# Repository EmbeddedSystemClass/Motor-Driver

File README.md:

# Motor-Driver

Collection of all boards past and presenet used by UOE Racing. Boards are organized by year of competition

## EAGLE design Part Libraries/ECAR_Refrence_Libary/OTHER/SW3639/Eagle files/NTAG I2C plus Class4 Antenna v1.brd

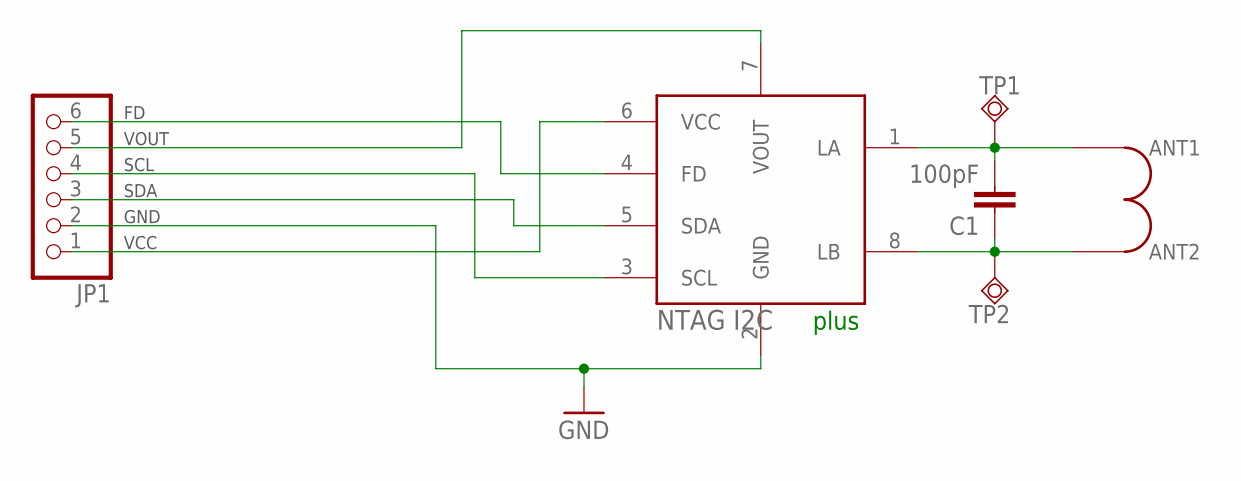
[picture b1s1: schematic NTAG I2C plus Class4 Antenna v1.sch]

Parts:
C1: 100pF; C0402K
JP1: PINHD-1X6/90; 1X06/90
TP1, TP2: TPSQPAD1-13; P1-13
U$1: ENERGY-HARVESTING_3-TURNS54X27_3TURN_THIN; 54X27_3TURNS_THIN
U$3: NTAG_I2CXQFN8; SOT902-3

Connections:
GND: JP1.2, U$3.2 (GND)
unnamed: C1.2, TP1.TP, U$1.ANT1, U$3.1 (LA)
unnamed: C1.1, TP2.TP, U$1.ANT2, U$3.8 (LB)
unnamed: JP1.1, U$3.6 (VCC)
unnamed: JP1.3, U$3.5 (SDA)
unnamed: JP1.4, U$3.3 (SCL)
unnamed: JP1.6, U$3.4 (FD)
unnamed: JP1.5, U$3.7 (VOUT)

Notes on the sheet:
VOUT
SCL
SDA
GND
VCC
plus

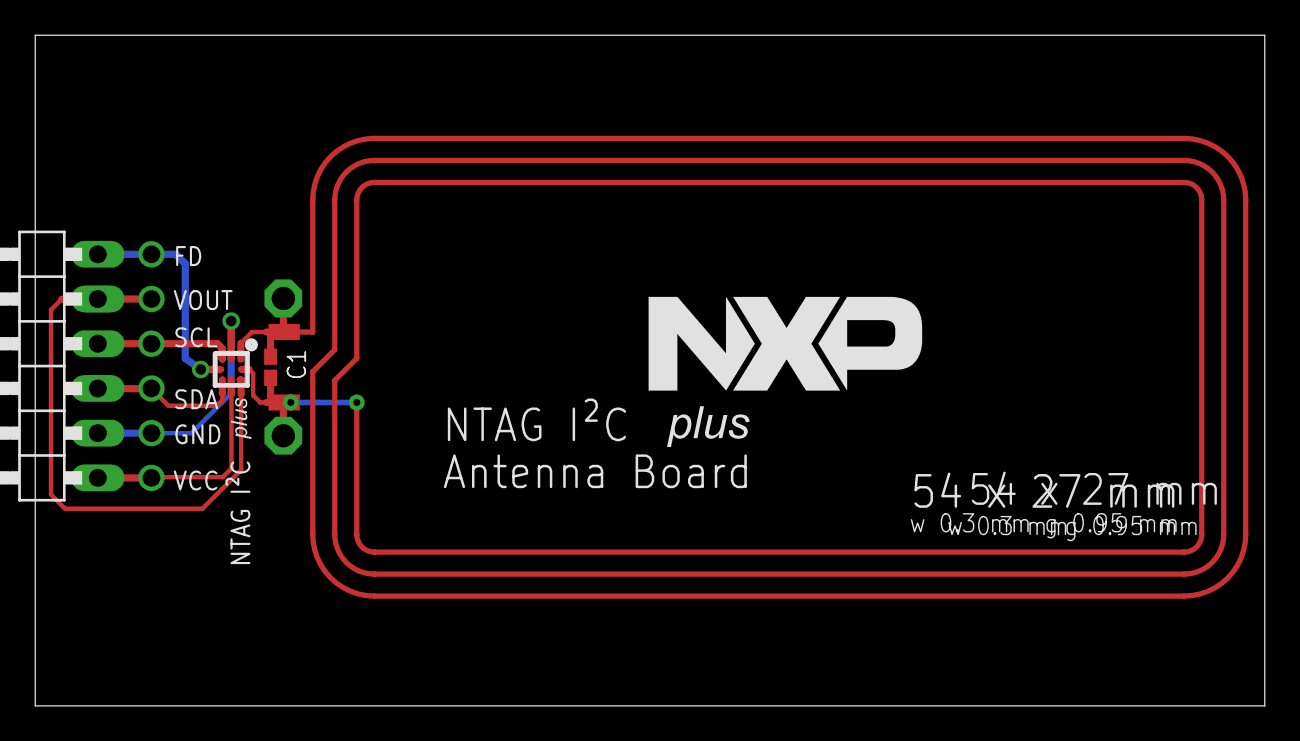
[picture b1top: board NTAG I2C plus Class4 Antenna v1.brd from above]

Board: 2 copper layers, 69.8 x 38.1 mm, 6 parts (0 on the bottom side), 8 nets.

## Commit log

2019-07-14 Addition of all files from 2018-2019
2019-07-14 Addition of part libaries and gitignore
2019-07-15 Creation of 2020 board project
2019-07-19 Reoranization
    Brought the old board project into Motor Folder 2019-2020
    Reorganization of project folder
2019-09-01 test1
2019-09-03 LM regulator
2019-09-15 changed net on nSHN
2019-09-25 Addition of input filter on throttle and the addition of the hall effect input digital gates (Schmitt and level translation)
2019-09-26 Fix of schematic layout and symbols for 3.3V and 5V power supply. Initial work on MOSFET power bridge
2019-09-27 Addition of SD Card, addition of the tempature sensors for Fets. Completion of motor driver chip circuit, completion of the FET power stage.
2019-09-27 Additon of the encoder input interface. Also added in the input connector circuits for the encoder and hall effect sensors
2019-10-10 A crazy amount of components added. MCU and Digital Interfaces and Connectors and Inputs schematic pages finished, same as Power section sheet
2019-10-17 Fixed Output Reg Pwr
2019-10-19 small adjustments to 3.3reg and renaming couple of components
2019-10-24 Some minor cosmetic fixes to the sheet
2019-11-01 Addition of power anaylsis
    Added the power analysis for the 3.3V and 5V power rials into the 2020 folder
2019-11-05 Addition of 5v regulator and led indication circuitry
2019-11-05 Generation of schematic for design review
2019-11-07 modification
    zero ohm resistors, labeling, zener, encoder enable
2019-11-08 Update ProjectGroup.DsnWrk
    Added to PMOS encoder enable configuration. Added parts
2019-11-15 Change of the throttle filter op-amp to address bandwidth and input bias problems. Also added simulation circuit and results in the simulation folder
2019-11-17 Re organization of a couple of schematic pages
2019-11-20 Checking of more blocks of the schematic.
    Removed the io expander, as its functionality is now covered by the expanded MCU socket.
    Changed the capacitors for the voltage input to the board. Simulated the voltage feedback circuit and then changed a resistor value to allow operation of the circuit up to 60V. Caps still need to be 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
2019-11-22 Addition of power filter simulation files
2019-11-25 some foot print changes and sanity checking
2019-11-25 sanity checking
2019-12-01 Changes to the schematic. Almost at completion
2019-12-03 Checking of the DRV circuit
2019-12-03 Fix of the led indicator circuits.
    Also changed the 47nF capacitor to have a rating of 100V so that the board can work at 60V (was 50V rated before)
2019-12-05 Verification of the FET bridge
2019-12-08 Update of the main power in connector to the bolt on board 4 pin variant. Should cut down on the amount of heating seen at the connector
2019-12-08 Change of main phase connector from 3 pin to 6 pin to increase current capability and allow for a more robust connector
2019-12-12 Final checks performed. Schematic should be ready for board creation
2020-01-03 Push of the initial layout
2020-01-04 Throttle section practice
2020-01-04 More practicing, placed Schmitt hall Schmit components
2020-01-05 Added the Encoder section
2020-01-05 net fixing
2020-01-05 moving buffer
2020-01-05 GPIO buffers and connectors
2020-01-06 Power section and driver chip finished
2020-01-11 Fix?
2020-01-11 Hopefully the right files
2020-01-13 Testest
    Commiting finaly
2020-01-15 placing GPIO buffer
    testing git
2020-01-15 More placing of test points
    git working
2020-01-16 Added 5v power
    Practicing with the polygon pour. May need to change and edit.
2020-01-16 Getting close to complete
2020-01-17 Revert "Merge branch 'master' of github.com:UOERacing/Motor-Driver"
    This reverts commit 896bb1447881fe9900ef6cad67ef5cf2d1325141, reversing
    changes made to bacd3aeafff96990d78e3a7c32f37b9bf0d5d698.
2020-01-18 Completion of routing
2020-01-19 Footprint fix, silk screen fixing and TP naming
2020-01-21 silk screen fixing
2020-01-22 Almost done silk screen
2020-01-23 Silk screen finished. Needs review
2020-01-23 Testing version control
2020-01-26 Change of mounting hole size to 3.5mm as per Simons instructions
2020-01-26 Minor silk correction and pass of the DRC
2020-01-27 Small finishing touches to the board. Now missing only logo for team
2020-01-27 Project ready for Review
2020-01-31 Footprint Fixes, Silk Screen Fix.
    Polygon pour at the 3v3 regulator Inductor needs some adjusting as well as some component placement
2020-02-03 Addition of Gerber files and fix of polygon attached to inductor. Slight silkscreen changes
2020-02-07 Tied the enable for the 3.3V regulator to the pwr good indicator of the 5V Regualtor
2020-02-08 Revert "na"
    This reverts commit 1781cdccb237cffe15a9127709c46b1f825b080e.
2020-02-11 Addition of enable pull up resistor on 3.3V regulator in case the power good line from 5V is not working correctly
2020-02-11 C13, 15, 16 rerouted due to voltage tolerances not being high enough . C15 changed to meet requirement and placed on board
2020-02-12 Capacitor Update finished
2020-02-16 ActiveBom File created
2020-02-27 Generation of RFM rev manufacturing files
2020-05-09 Additions to parts library for transmitter

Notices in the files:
parts and their libraries:
SparkFun-Aesthetics: Licensing: Creative Commons ShareAlike 4.0 International - https://creativecommons.org/licenses/by-sa/4.0
